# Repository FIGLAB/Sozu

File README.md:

# Sozu: Self-Powered Radio Tags for Building-Scale Activity Sensing

## About
Sozu a low-cost self-powered activity sensing system, which can detect a wide range of events wirelessly, through walls and floors, at a whole-building scale. Instead of running on batteries, Sozu tags leverage energy from activities that they sense, and convert this energy into RF broadcasts, acting like miniature radio stations. More information about this project can be found below:

[[Project video]](https://youtu.be/wbq-eOOIPyw) [[Paper]](https://yangzhang.dev/research/Sozu/Sozu.pdf) [[Citation format]](https://doi.org/10.1145/3332165.3347952)

## Sozu Toolkit
To facilitate others' hands-on experience with Sozu, we created a toolkit which consists of a solar powered Sozu tag, an RTL-SDR, a set of antennas, demo code, and a quick start guide:

### Step 1: Make sure you have everything
You will find the following parts in the box:
*  A Sozu tag powered by a small [solar panel](https://www.digikey.com/product-detail/en/panasonic-bsg/AM-8801CAR/869-1016-ND/2165201)
*  One alligator clip
*  [RTL-SDR + antenna](https://www.amazon.com/dp/B011HVUEME/ref=cm_sw_em_r_mt_dp_U_lSCGCbVDHKKQQ)

### Step 2: Connect the SDR with antenna (two long ones), and connect it to the laptop:

### Step 3: Install software

Sozu receiver is based on SDR. In this tutorial, we will use RTL-SDR. The easiest way to get data out of RTL-SDR is to use [pystlsdr](https://nocarryr.github.io/pyrtlsdr/) -- A Python wrapper for librtlsdr (a driver for Realtek RTL2832U based SDR’s). Python3 is required (3.7.4 was tested).

Steps to below to install librtlsdr and run Sozu demo code:

1. Install pyrtlsdr via [pip](https://pip.pypa.io/en/stable/):  

```bash
pip install pyrtlsdr
```

2. Install librtlsdr via [brew](https://brew.sh):  

```bash
brew install librtlsdr
```

3. Download Project Sozu source code from the [Github Page](https://github.com/FIGLAB/Sozu) or

```bash
git clone git@github.com:figlab/Sozu.git
```

4. Now plug in the SDR with the antenna connected (through USB) and get the RF signal from your environment by running the python code (./toolkit/software/Python/demo_waterfall.py):

```bash
python demo_waterfall.py
```

If you can see the above output on your python window, you are ready to receive RF signals from Sozu tags!

### Step 4: Deploy Sozu tag in the environment
1. Deploy harvesters in the environment.

2. If you use a different energy harvester, use a multimeter to make sure the harvester provides higher than 1.5 Volts from the activity that you are interested in sensing.

3. Connect the energy harvester to the Sozu tag.

### Step 5: Locate the Sozu signal on the frequency spectrogram

1. Run the Python server code(./toolkit/software/Python/demo_waterfall_server.py):

2. Tune the center frequency of your SDR around the Sozu tag frequency (labeled on the back of the tag), until you see its signal on the waterfall chart:

After you have located the signal, you are ready to make applications out of it!

### Step 6 (optional):  Visualize and process Sozu signals with other programs

The Python code (./toolkit/software/Python/demo_waterfall_server.py) functions like a TCP server, ready to stream data out to any programs you want to use in your project. Here we demonstrate getting Sozu signals with Processing.

1. Download and install Processing from [https://processing.org](https://processing.org)

2. Run the Processing client code (./toolkit/software/Processing/client/client.pde). Now you should see the Sozu signal shown in the Processing app:

3. Finally, connecting the alligator cable to the tag antenna as an extension helps improve the broadcast range.

### Request Sozu Toolkit
Please fill out the google form below for your toolkit request: https://forms.gle/UTFnRSarYxjS2oz19

For bulk orders and commercial collaborations, please email us at info@figlab.com

## Other Resources

### What does the name Sozu mean

Sozu – comes from the traditional Japanese water feature, where a bamboo segment slowly fills with water, eventually causing its center of mass to shift, such that it pivots downwards, striking a rock (designed to scare away animals in gardens). This is similar in principle to our system, where one form of energy is converted into another for practical use.

### See what others created with Sozu
Auxiliary video of example projects: https://youtu.be/Q_soA7qurLE

### Sozu tags
PCB design files: https://github.com/FIGLAB/Sozu/tree/master/pcb

### Gqrx
[Gqrx](http://gqrx.dk) is a useful software to interface SDRs with a nice UI, which you can use and tune many parameters (e.g., sampling rate, center frequency, averaging etc.) for debug.

### Common issues

#### Cannot find Sozu tag frequency
Solution: Try to move the Sozu tag closer to the receiver. It is also possible that Sozu tag frequency shifted since the spacing of the inductor coil and the trimmer capacitor might change over shipping. To locate tag frequency, please tune the center frequency of your spectrogram visualizer around the labeled frequency on the back of the Sozu tag. It is easier to locate the frequency with Gqrx and use a SDR with wider bandwidth (e.g., [HackRF](https://greatscottgadgets.com/hackrf/one/) has a 20MHz bandwidth)

#### OSError: Error code -3 when opening SDR (device index = 0)
Solution: Unplug the SDR from the USB, and plug it back in.

#### AttributeError: dlsym(RTLD_DEFAULT, rtlsdr_get_device_count): symbol not found
Solution: Try brew install librtlsdr again.

## Contact
yang.zhang@cs.cmu.edu

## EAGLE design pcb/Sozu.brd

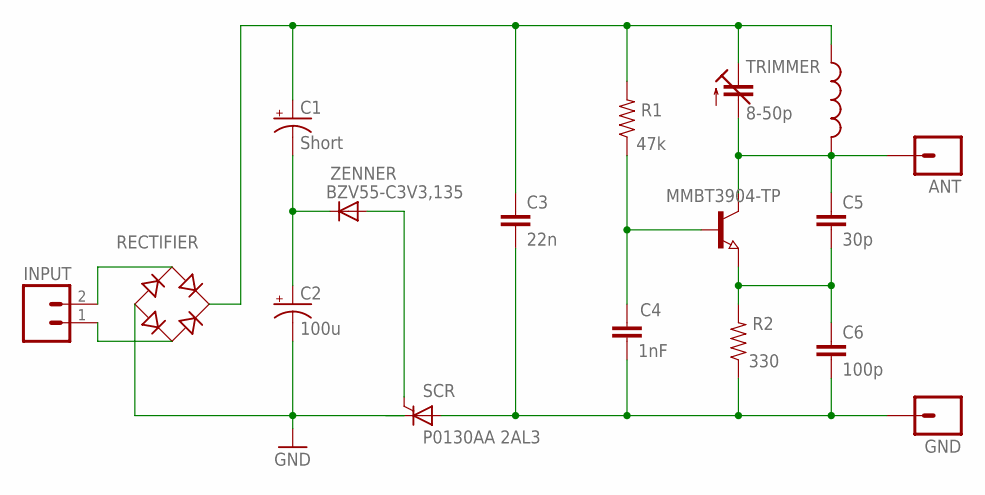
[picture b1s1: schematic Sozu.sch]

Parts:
ANT: M01PTH; 1X01
C1: Short; ENERGY_CAP_2312
C2: 100u; ENERGY_CAP_2312
C3: 22n; 0603-CAP
C4: 1nF; 0603-CAP
C5: 30p; 0603-CAP
C6: 100p; 0603-CAP
GND: M01PTH; 1X01
INPUT: M02PTH; 1X02
Q1: MMBT3904-TP; SOT23
R1: 47k; 0603-RES
R2: 330; 0603-RES
RECTIFIER: SOZU_RECTIFIER; RFTAG_RECTIFIER
SCR: P0130AA 2AL3; TO92-2
TRIMMER: 8-50p; SPARKFUN-CAPACITORS_GRM43D
U$2: SOZU_INDUCTOR
ZENNER: BZV55-C3V3,135; SOD-123

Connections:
COLLECTER: ANT.1, C5.1, Q1.3 (C), TRIMMER.A, U$2.2
GND: C2.2 (-), RECTIFIER.P$4 (-), SCR.C
unnamed: INPUT.2, RECTIFIER.P$1 (AC1)
unnamed: C1.2 (-), C2.1 (+), ZENNER.C
unnamed: SCR.G, ZENNER.A
unnamed: INPUT.1, RECTIFIER.P$2 (AC2)
unnamed: C5.2, C6.1, Q1.2 (E), R2.2
unnamed: C4.1, Q1.1 (B), R1.1
VDC: C1.1 (+), C3.1, R1.2, RECTIFIER.P$3 (+), TRIMMER.C (E), U$2.1
V_GND: C3.2, C4.2, C6.2, GND.1, R2.1, SCR.A

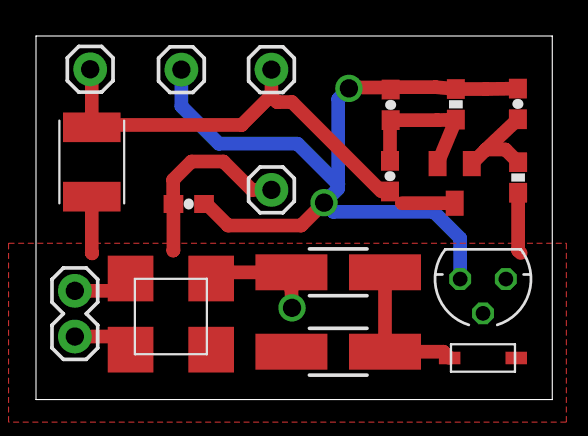
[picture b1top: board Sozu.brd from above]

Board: 2 copper layers, 28.7 x 20.2 mm, 17 parts (0 on the bottom side), 10 nets.

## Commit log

2019-07-12 Added toolkit materials
2019-07-12 Fixed broken link
2019-07-12 Added placeholder for the example energy harvesting page
2019-09-26 Added pcb design files
2019-09-26 Added latest readme
2019-10-11 Updated main page readme
2019-10-14 Added google form
2019-10-14 Updated readme files
2019-10-16 Added video link of example projects
2019-10-16 Removed the example folder
2019-10-18 Added youtube video link
2019-10-18 Updated several urls
2019-10-19 Added Sozu gif
2019-10-19 Added Gqrx

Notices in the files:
parts and their libraries:
SparkFun-Connectors: Licensing: Creative Commons ShareAlike 4.0 International - https://creativecommons.org/licenses/by-sa/4.0
